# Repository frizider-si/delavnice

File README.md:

# Delavnice v Frižiderju

Za Frižiderjeve delavnice največkrat pripravimo kakšna navodila. Ta lahko seveda uporabljaš tudi izven Frižiderja, doma, ali pa kjerkoli. V navodilih so tudi dostikrat kakšna vprašanja, ali pa izzivi. Jih znaš rešiti?

Navodila so dostopna naslednje delavnice:

* [Bombardiranje z droni](./bombardiranje-z-droni)
* [Pametna hisa](./pametna-hisa)
* [Zaslon iz vetrnice](zaslon-iz-vetrnice)
* [Spoznavanje Arduina](spoznavanje-arduina)

Delavnice, ki smo jih izvedli, pa za njih navodila šele pripravljamo, so:

* [Avtonomno vozilo](./avtonomno-vozilo/)
* [Cepelini](./dron-cepelin/)

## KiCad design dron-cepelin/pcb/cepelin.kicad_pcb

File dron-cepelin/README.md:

# Cepelini

Namen delavnice je sestaviti cepelin, ki ga upravljamo s pomočjo IR daljinca.

Cepelin sestavljajo naslednje komponente:
* Balon napolnjen s helijem,
* mikrokontroler atmega328p,
* H-bridge(2x LB1973),
* senzor vlage(MS5607),
* temperaturni senzor(SHT21),
* IR sprejemnik,
* motorji s propelerji,
* dve led diodi.

Spodaj je objavljen primer kode, ki omogoča upravljanje cepelina s pomočjo IR daljinca.

    #include <IRremote.h>
    #include <Wire.h>
    #include <SHT2x.h>

    // Commands used to control motors
    #define FORWARD PORTC = (PORTC & ~0b0001111) | 0b00000101 
    #define STOP_F PORTC = (PORTC & ~0b0001111) | 0b00000000 
    #define BACKWARD PORTC = (PORTC & ~0b0001111) | 0b00001010 
    #define DOWNWARD PORTB = (PORTB & ~0b0000011) | 0b00000010 
    #define STOP_UD PORTB = (PORTB & ~0b0000011) | 0b00000000 
    #define UPWARD PORTB = (PORTB & ~0b0000011) | 0b00000001 
    #define LEFT_T PORTC = (PORTC & ~0b0001111) | 0b00001001
    #define RIGHT_T PORTC = (PORTC & ~0b0001111) | 0b00000110
    
    // IR recv pin
    #define RECV_PIN 0
    
    #define LED_BLINKING_SPEED 500
    #define MOTOR_ON_TIME 300
    
    // SENSOR_MODE indicates which sensor is currently being read
    typedef enum {TEMPERATURE, PRESSURE, HUMIDITY} SENSOR_MODE;
    // SENSOR_STAGE is used to distinguish between sensor reading stage and led blinking stage
    typedef enum {READING, INDICATING} SENSOR_STAGE;
    // Led modes
    typedef enum {ON, OFF} LED_MODE;
    
    // Other vars and objects
    IRrecv irrecv(RECV_PIN);
    byte leds[3] = {2, 3};
    decode_results results;
    
    void setup(){
      
      // Set the motor pins to ouput
      pinMode(8, OUTPUT); 
      pinMode(9, OUTPUT); 
      pinMode(12, OUTPUT); 
      pinMode(13, OUTPUT); 
      pinMode(14, OUTPUT); 
      pinMode(15, OUTPUT);     
      pinMode(16, OUTPUT); 
      pinMode(17, OUTPUT);
      
      // Set pins for diodes to OUTPUT
      pinMode(leds[0], OUTPUT);
      pinMode(leds[1], OUTPUT);
      pinMode(4, OUTPUT);
      
      // Start the receiver
      irrecv.enableIRIn();
      
      // Init i2c
      Wire.begin();
    
    }
    
    void loop(){
      
      // Show temperature and humidity by means of a blinking LEDs
      showSensorMeasurements();
      
      // Turn on motors if any of the control buttons is pressed
      IRRemoteRunAction();
    }
    
    void showSensorMeasurements(){
    
      static SENSOR_MODE s_mode = TEMPERATURE;
      static SENSOR_STAGE stage = READING;
      static LED_MODE l_mode = ON;
      static unsigned long lastTime;
      static long readings;
      static byte digit;
      static byte ledIndex;
      
      if(millis() - lastTime >= LED_BLINKING_SPEED){
        lastTime = millis();
        if(stage == READING){
          if(s_mode == TEMPERATURE){
            readings = SHT2x.GetTemperature();
            // Change stage
            stage = INDICATING;
            digitalWrite(4, HIGH);
          }
          else if(s_mode == HUMIDITY){
            readings = SHT2x.GetHumidity();
            // Change stage
            stage = INDICATING;
            digitalWrite(4, LOW);
          }
          // First digit
          digit = readings % 10;
        }
        else if(stage == INDICATING){ 
          if(readings == 0){
            s_mode == HUMIDITY ? s_mode = TEMPERATURE : s_mode = HUMIDITY;
            stage = READING;
            ledIndex = 0;
          }
          else if(digit == 0){
            readings = readings / 10;
            digit = readings % 10;
            ledIndex++;
           }
          // Blink
          else if(digit > 0){
            if(l_mode == ON){
              digitalWrite(leds[ledIndex], HIGH);
              l_mode = OFF;
            }
            else if(l_mode == OFF){
              digitalWrite(leds[ledIndex], LOW);
              digit--;
              l_mode = ON;
            }
          }
        }
      }
    }
    
    void IRRemoteRunAction(){
      
      static unsigned long lastTime;
      
      if(irrecv.decode(&results)) {
        switch(results.value){
          case 0x112005A:
            FORWARD;
            break;
          case 0x11200DA:
            BACKWARD;
            break;
          case 0x11200BA:
            RIGHT_T;
            break;
          case 0x112003A:
            LEFT_T;
            break;
          case 0x1120009:
            UPWARD;
            break;
          case 0x112005E:
            DOWNWARD;
            break;
        }
        lastTime = millis();
        irrecv.resume(); // Receive the next value
      }
      
      // Check if time is elapsed
      if(millis() - lastTime >= MOTOR_ON_TIME){
        // Stop motors 
        STOP_F;
        STOP_UD; 
      }
      
    }

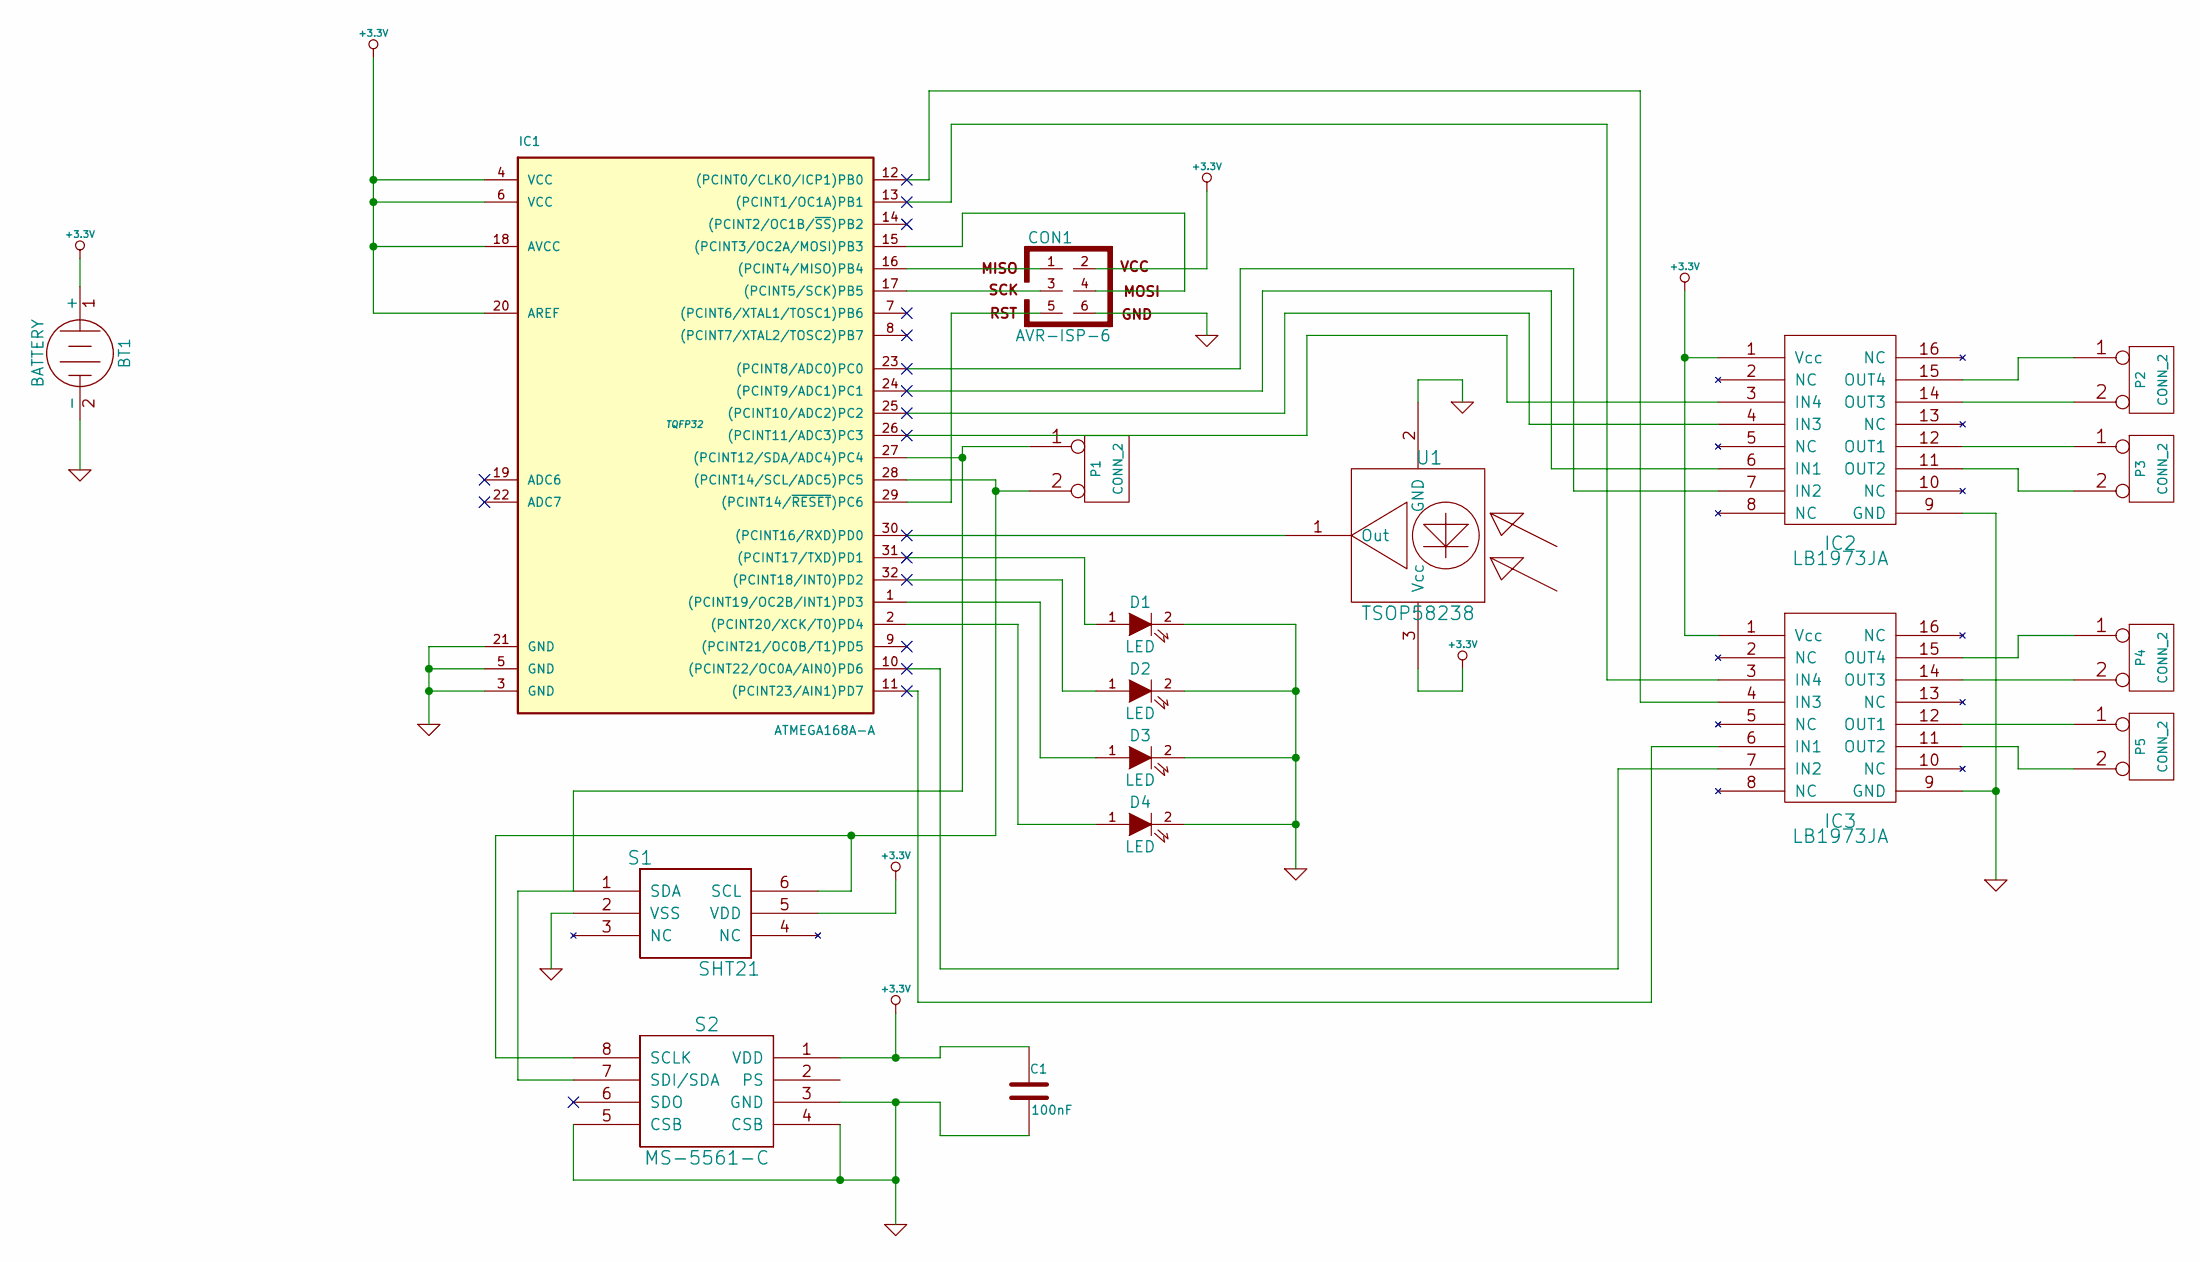
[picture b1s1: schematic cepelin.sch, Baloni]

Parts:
BT1: BATTERY
C1: 100nF
CON1: AVR-ISP-6
D1, D2, D3, D4: LED
IC1: ATMEGA168A-A; TQFP32
IC2, IC3: LB1973JA
P1, P2, P3, P4, P5: CONN_2
S1: SHT21
S2: MS-5561-C
U1: TSOP58238

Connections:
+3.3V: BT1.1 (+), C1.1, CON1.2, IC1.4 (VCC), IC1.6 (VCC), IC1.18 (AVCC), IC1.20 (AREF), IC2.1 (Vcc), IC3.1 (Vcc), S1.5 (VDD), S2.1 (VDD), U1.3 (Vcc)
GND: BT1.2 (-), C1.2, CON1.6, D1.2 (K), D2.2 (K), D3.2 (K), D4.2 (K), IC1.3 (GND), IC1.5 (GND), IC1.21 (GND), IC2.9 (GND), IC3.9 (GND), S1.2 (VSS), S2.3 (GND), S2.4 (CSB), S2.5 (CSB), U1.2 (GND)
unnamed: D4.1 (A), IC1.2 ((PCINT20/XCK/T0)PD4)
unnamed: D3.1 (A), IC1.1 ((PCINT19/OC2B/INT1)PD3)
unnamed: D2.1 (A), IC1.32 ((PCINT18/INT0)PD2)
unnamed: IC1.30 ((PCINT16/RXD)PD0), U1.1 (Out)
unnamed: D1.1 (A), IC1.31 ((PCINT17/TXD)PD1)
unnamed: IC2.14 (OUT3), P2.2 (PM)
unnamed: IC2.12 (OUT1), P3.1
unnamed: IC1.23 ((PCINT8/ADC0)PC0), IC2.7 (IN2)
unnamed: IC1.24 ((PCINT9/ADC1)PC1), IC2.6 (IN1)
unnamed: IC1.25 ((PCINT10/ADC2)PC2), IC2.4 (IN3)
unnamed: IC1.26 ((PCINT11/ADC3)PC3), IC2.3 (IN4)
unnamed: IC3.14 (OUT3), P4.2 (PM)
unnamed: IC3.12 (OUT1), P5.1
unnamed: IC1.10 ((PCINT22/OC0A/AIN0)PD6), IC3.7 (IN2)
unnamed: IC1.13 ((PCINT1/OC1A)PB1), IC3.3 (IN4)
unnamed: IC2.15 (OUT4), P2.1
unnamed: IC2.11 (OUT2), P3.2 (PM)
unnamed: IC3.11 (OUT2), P5.2 (PM)
unnamed: IC3.15 (OUT4), P4.1
unnamed: IC1.11 ((PCINT23/AIN1)PD7), IC3.6 (IN1)
unnamed: IC1.12 ((PCINT0/CLKO/ICP1)PB0), IC3.4 (IN3)
unnamed: IC1.27 ((PCINT12/SDA/ADC4)PC4), P1.1, S1.1 (SDA), S2.7 (SDI/SDA)
unnamed: IC1.28 ((PCINT14/SCL/ADC5)PC5), P1.2 (PM), S1.6 (SCL), S2.8 (SCLK)
unnamed: CON1.5, IC1.29 ((PCINT14/~RESET~)PC6)
unnamed: CON1.4, IC1.15 ((PCINT3/OC2A/MOSI)PB3)
unnamed: CON1.3, IC1.17 ((PCINT5/SCK)PB5)
unnamed: CON1.1, IC1.16 ((PCINT4/MISO)PB4)

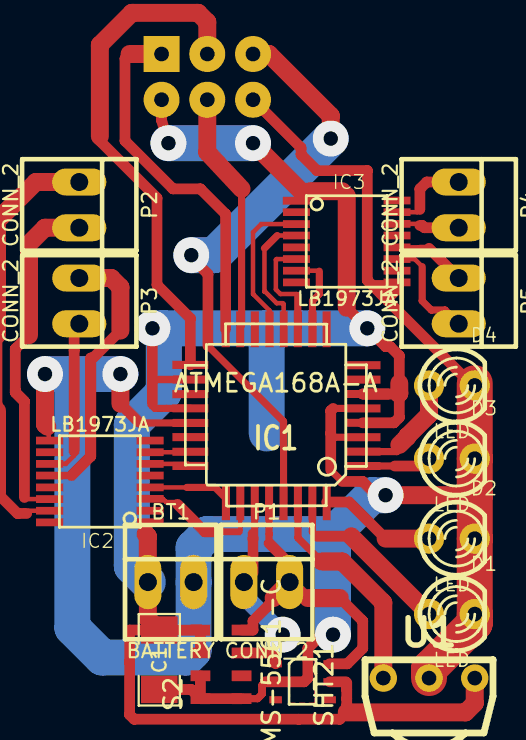
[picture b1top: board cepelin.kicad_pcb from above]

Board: 2 copper layers, 18 parts (1 on the bottom side), 29 nets.

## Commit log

2015-10-30 Zdruzena besedila delavnic.
2015-10-30 Dodaj delavnico Zaslon iz vetrnice
2015-11-03 Prvi del bombadrona.
2015-11-03 Popravki slik, zacetne strani.
2015-11-04 Dodano delo z LCD.
2015-11-04 Nekaj popravkov in novih slik.
2015-11-04 Zmanjsanje slike.
2015-11-04 Uskladitev velikosti naslovov.
2015-11-04 Manjsa slika.
2015-11-11 Razdelitev po poglavjih, novo poglavje o prekinitvah.
2015-11-12 Poravnava kode.
2015-11-13 Manjsi slovnicni popravki.
2015-11-14 Rename ucni-list.md to README.md
2015-11-14 Zdruzi zaslon-iz-vetrnice v README.md
2015-11-16 Urejanje zaslon-iz-vetrnice
2015-11-19 Stilski popravki na glavni strani.
2015-11-19 Merjenje hitrosti.
2015-11-19 Nova slika.
2015-11-19 Popravki.
2015-11-26 Zadnja delavnica
2015-11-26 Sprememba imena
2015-11-26 Last chapter added
2015-12-01 added code
2015-12-01 added figures
2015-12-07 Dodana slika vozila
2015-12-07 Dodana slika cepelina
2016-04-13 Spoznavanje Arduina: prvi stirje deli in pol
2016-04-19 Spoznavanje: 05 Merjenje temperature
2016-05-01 Spoznavanje Arduina: 05 Mikrofon
2016-05-02 Spremeni vrstni red 4, 5 + različni popravki v njima
2016-05-02 Spoznavanje Arduina: 6 - Semafor
2016-05-02 Spoznavanje Arduina: README.md
2016-05-03 Dodaj Spoznavanje Arduina v README.md
2016-05-12 Licenca
2016-10-23 Spremembe ob PSD
